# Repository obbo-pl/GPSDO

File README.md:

# GPSDO
GPS Disciplined Oscillator

##### Main features:

- 2 outputs 40MHz square wave, signal level 3.3V,
- 1pps, signal level 3.3V,
- for 40MHz output, error less than 0.15ppm,
- frequency verification every 2 seconds,
- stabilization of the frequency after about 80 seconds from the appearance of the 1pps signal,
- accomplishment of stabilization signaled by the logic level at the "FIX" output,
- automatic building of temperature characteristics,
- stabilization based on the temperature characteristic with an error of less than 0.3ppm, 
- supply voltage 5V,
- current consumption about 130mA,
- transparent transmission of messages from and to the U-BLOX module,
- parameter control via serial port (19200bps), 

For more information: [www.obbo.pl](https://obbo.pl/gpsdo)

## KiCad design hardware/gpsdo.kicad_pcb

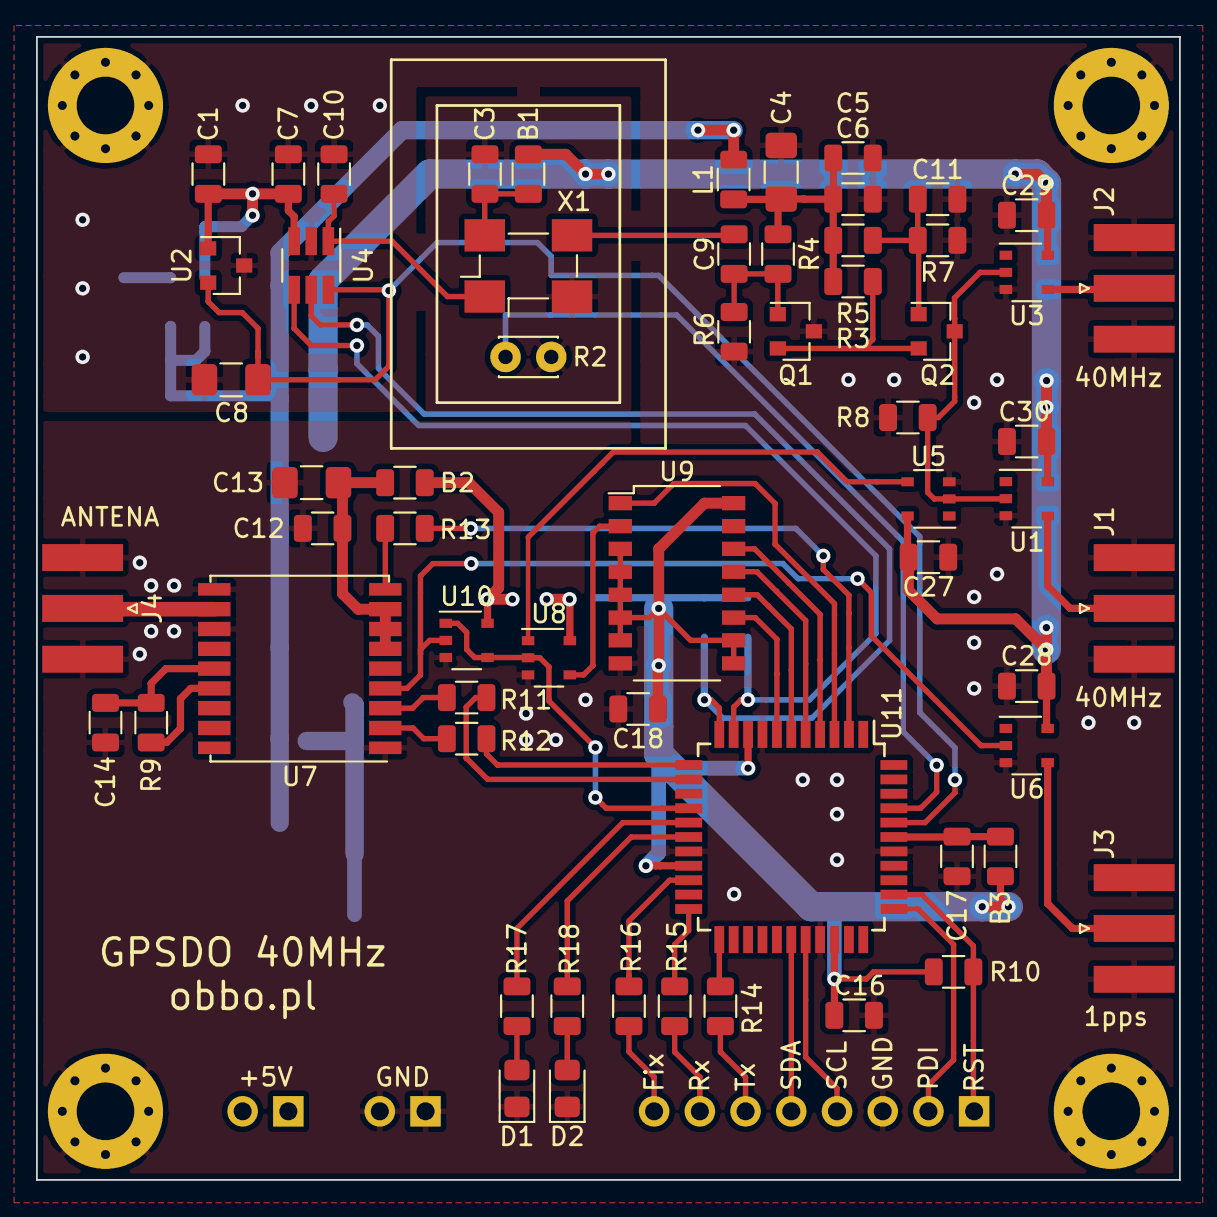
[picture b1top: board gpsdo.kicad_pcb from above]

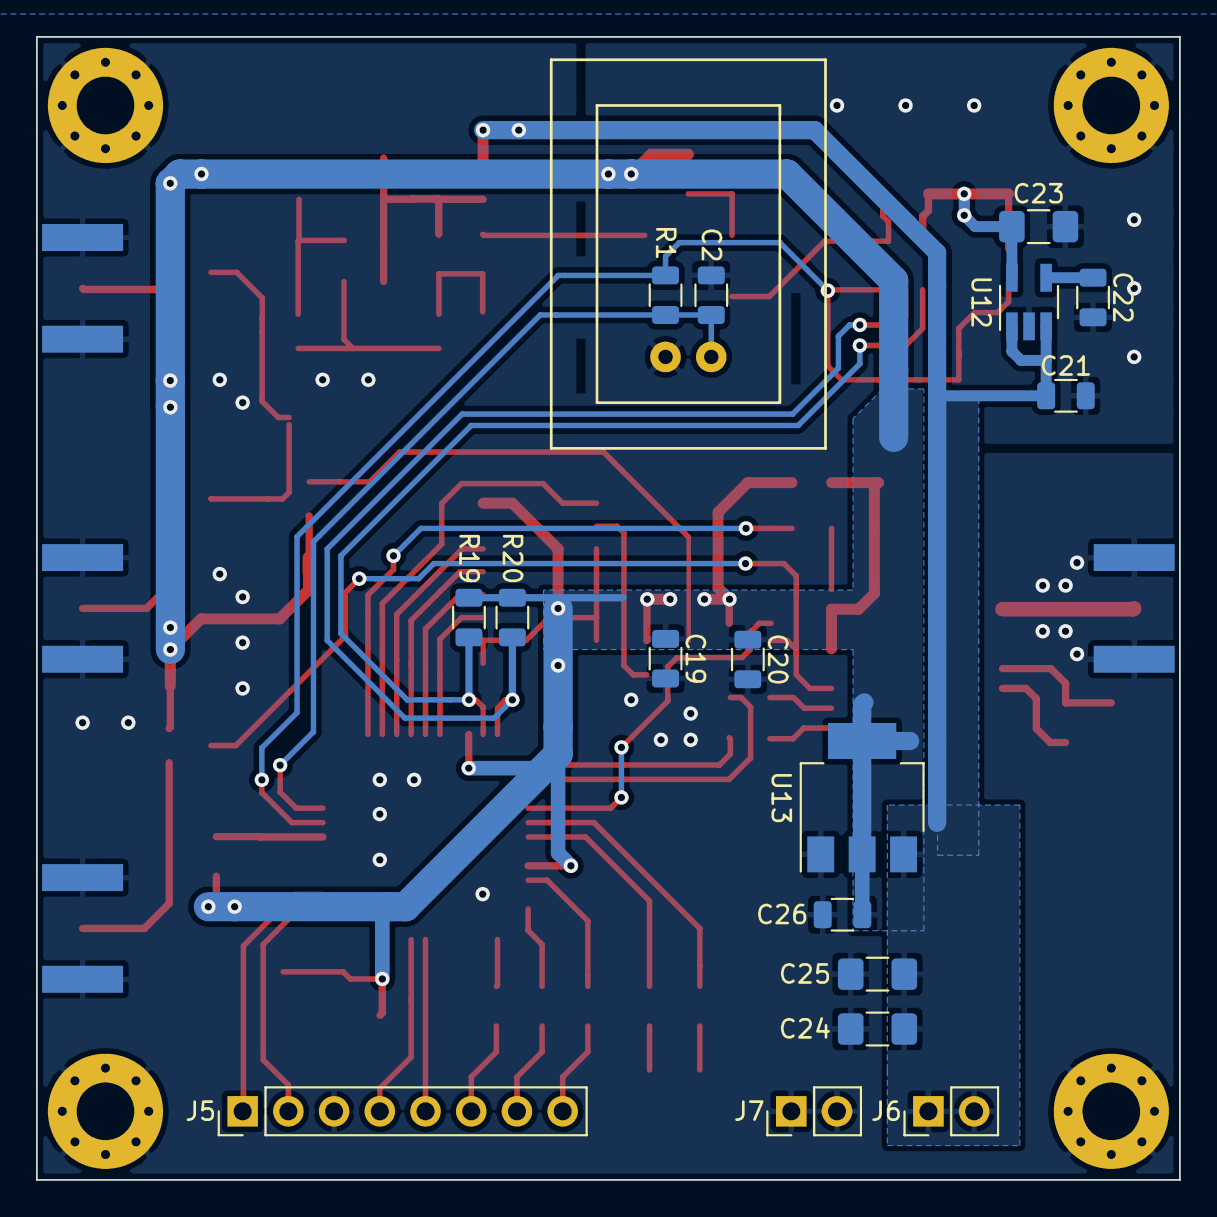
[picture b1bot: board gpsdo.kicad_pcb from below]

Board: 2 copper layers, 63.5 x 63.5 mm, 82 parts (17 on the bottom side), 54 nets.

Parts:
B1, B2, B3: bead; R_0805K
C1, C2, C3, C5, C7, C10, C12, C16, C17, C18, C21, C22, C26: 100n; C_0805K
C4: 4u7; C_1206_3216Metric_Pad1.42x1.75mm_HandSolder
C6, C9, C11, C14, C19, C20, C27, C28, C29, C30: 10n; C_0805K
C8: 2u2; C_1206_3216Metric_Pad1.42x1.75mm_HandSolder
C13, C23, C24, C25: 10u; C_1206_3216Metric_Pad1.42x1.75mm_HandSolder
D1, D2: LED; LED_0805_2012Metric_Pad1.15x1.40mm_HandSolder
H1, H2, H3, H4: MountingHole_Pad; MountingHole_3.2mm_M3_Pad_Via
J1, J2, J3, J4: Conn_Coaxial; SMA_EdgeMount
J5: Conn_01x08; PinHeader_1x08_P2.54mm_Vertical
J6, J7: Conn_01x02; PinHeader_1x02_P2.54mm_Vertical
L1: 220n; L_0805K
Q1, Q2: MMBT3906LT1G; SOT-23
R1: 10k; R_0805K
R2: PTC-SOD70; Thermistor_PTC_D2.0mm_W2.0mm_P2.54mm
R3: 100; R_0805K
R4, R5: 3k3; R_0805K
R6, R7: 6k8; R_0805K
R8: 330; R_0805K
R9: 10; R_0805K
R10: 22k; R_0805K
R11, R12, R13, R14, R15, R16: 220; R_0805K
R17, R18: 620; R_0805K
R19, R20: 2k2; R_0805K
U1, U3, U5, U6: 74LVC1G14; TSOP-5_1.65x3.05mm_P0.95mm
U2: MCP1525-TT; SOT-23
U4: MCP4726AxT-E-CH; SOT-23-6_Handsoldering
U7: MAX-M8W; ublox_MAX
U8: 74LVC1G08; TSOP-5_1.65x3.05mm_P0.95mm
U9: 74LVC161; SOP-16_4.4x10.4mm_P1.27mm
U10: 74LVC1G80; TSOP-5_1.65x3.05mm_P0.95mm
U11: ATxmega32A4U-AU; TQFP-44_10x10mm_P0.8mm
U12: TPS73633DBV; SOT-23-5_HandSoldering
U13: LM1117-3.3; SOT-223-3_TabPin2
X1: TCVCXO-I733-2P3-40MHz; Oscillator_SMD_ILSI-4Pin_5.0mm_3.2mm_HandSoldering

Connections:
1PPS: U6.2, U7.4, U10.2
1PPS_GATE: U8.2, U10.1, U10.4, U11.15
+3V3: B1.1, B2.1, B3.1, C16.1, C18.1, C19.1, C20.1, C26.1, C27.1, C28.1, C29.1, C30.1, R10.1, R19.1, R20.1, U1.5, U3.5, U5.5, U6.5, U8.5, U9.3, U9.4, U9.5, U9.6, U9.7, U9.9, U9.10, U9.16, U10.5, U11.9, U11.19, U11.31, U13.2
+5V: C21.1, C24.1, C25.1, J6.1, J6.2, L1.1, U12.1, U12.3, U13.3
CLK: U5.4, U8.1
FIX: R16.1, U11.20
GND: C1.2, C2.2, C3.2, C4.2, C5.2, C6.2, C7.2, C8.2, C10.2, C11.2, C12.2, C13.2, C14.2, C16.2, C17.2, C18.2, C19.2, C20.2, C21.2, C22.2, C23.2, C24.2, C25.2, C26.2, C27.2, C28.2, C29.2, C30.2, D1.1, D2.1, H1.1, H2.1, H3.1, H4.1, J1.2, J2.2, J3.2, J4.2, J5.3, J7.1, J7.2, Q1.3, R2.1, R6.2, R7.2, R8.2, U1.3, U2.3, U3.3, U4.2, U5.3, U6.3, U7.1, U7.10, U7.12, U8.3, U9.8, U10.3, U11.8, U11.18, U11.30, U11.38, U12.2, U13.1, X1.2
GPS_RESET: R13.2, U11.2
GPS_RX: R11.1, U11.13
GPS_TX: R12.2, U11.12
LED1: R17.1, U11.16
LED2: R18.1, U11.17
MR: U9.1, U11.3
unnamed: B1.2, C3.1, X1.4
unnamed: B2.2, C12.1, C13.1, U7.6, U7.7, U7.8
unnamed: B3.2, C17.1, U11.39
unnamed: C4.1, C5.1, C6.1, L1.2, R3.1, R4.1, R5.1
unnamed: C9.1, X1.3
unnamed: C9.2, Q1.1, R4.2, R6.1
unnamed: C11.1, Q2.1, R5.2, R7.1
unnamed: C14.1, R9.2, U7.14
unnamed: C22.1, U12.4
unnamed: D1.2, R17.2
unnamed: D2.2, R18.2
unnamed: J1.1, U1.4
unnamed: J2.1, U3.4
unnamed: J3.1, U6.4
unnamed: J4.1, U7.11
unnamed: J5.6, R14.2
unnamed: J5.7, R15.2
unnamed: J5.8, R16.2
unnamed: Q1.2, Q2.2, R3.2
unnamed: Q2.3, R8.1, U1.2, U3.2, U5.2
unnamed: R9.1, U7.15
unnamed: R11.2, U7.3
unnamed: R12.1, U7.2
unnamed: R13.1, U7.9
unnamed: U8.4, U9.2
OUT_RX: R15.1, U11.22
OUT_SCL: J5.4, U11.29
OUT_SDA: J5.5, U11.28
OUT_TX: R14.1, U11.23
PDI: J5.2, U11.34
Q0: U9.14, U11.4
Q1: U9.13, U11.5
Q2: U9.12, U11.6
Q3: U9.11, U11.7
RESET: J5.1, R10.2, U11.35
SCL: R20.2, U4.5, U11.11
SDA: R19.2, U4.4, U11.10
VDD: C1.1, C7.1, C23.1, U2.1, U4.3, U12.5
VREF2.5V: C8.1, R1.2, U2.2, U4.6, U11.40
VTEMP: C2.1, R1.1, R2.2, U11.41
Vadj: C10.1, U4.1, X1.1

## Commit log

2021-01-17 New terminal commands
2021-01-18 Decrease startup time
2021-01-18 Defined CSV delimiter
2021-01-23 Transparent access to the GPS module via the serial port
2021-01-23 Sample U-BLOX command
2021-02-20 maintaining the frequency-temperature characteristic
2021-03-23 Frequency correction based on temperature characteristics
2023-03-02 symbol update
